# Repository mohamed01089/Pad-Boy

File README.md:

# Pad Boy
A simple macropad consists of 5 switches, a rotary encoder, custom pcp, and a case

## Dimensions 

PCP dimensions: 60.5 mm * 62.5 mm.
Case dimensions: 80.9 mm * 82.9 mm.

## BOM

- 5x Cherry MX Kew Switches
- 1x Rotary Encoder Witch Switch
- Seeduino XIAO RP2040
- 3D Printing
- PCP Manifacture

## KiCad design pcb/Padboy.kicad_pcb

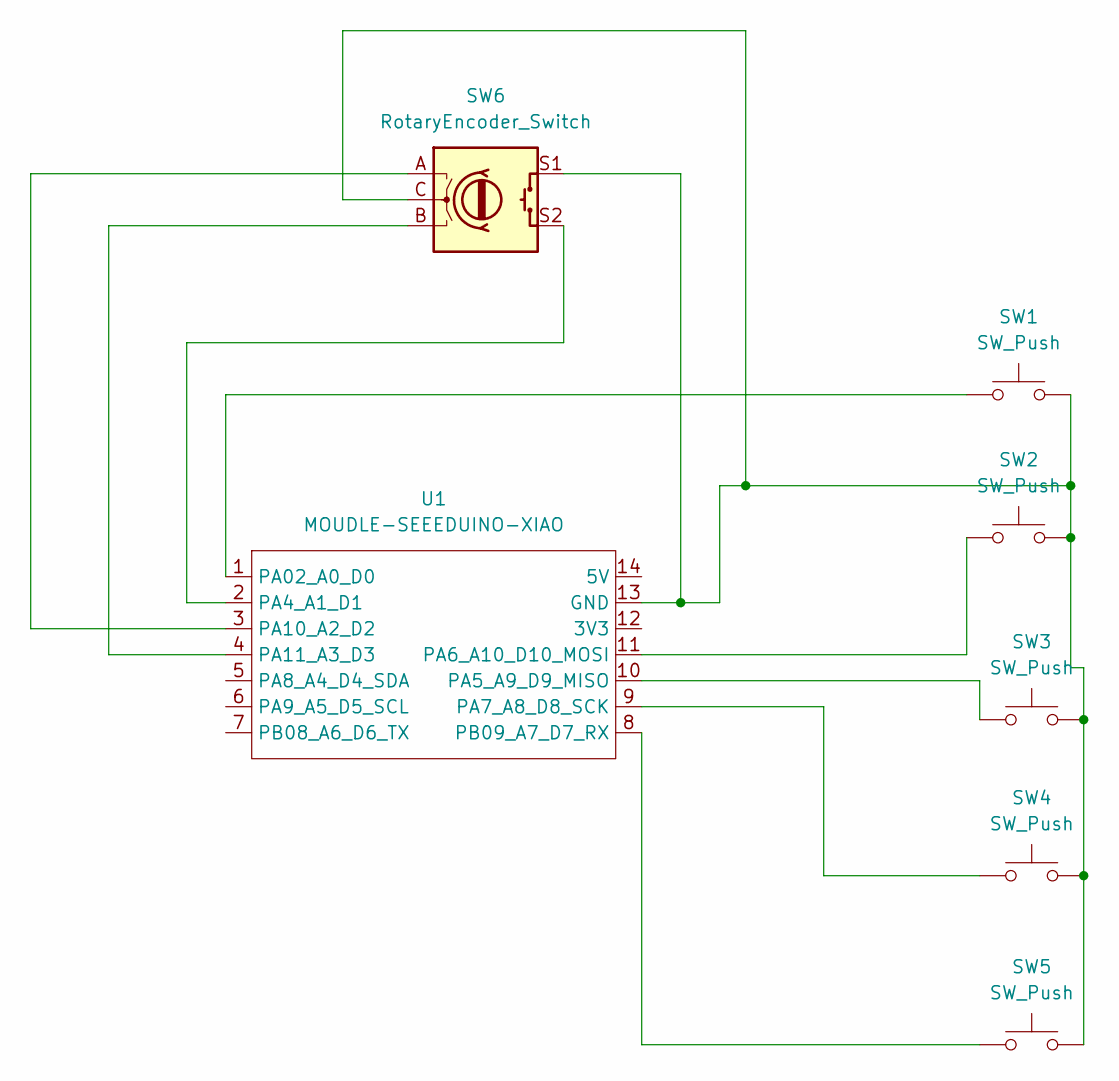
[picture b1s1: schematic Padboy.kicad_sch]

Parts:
SW1, SW2, SW3, SW4, SW5: SW_Push; SW_Cherry_MX_1.00u_PCB
SW6: RotaryEncoder_Switch; RotaryEncoder_Alps_EC11E-Switch_Vertical_H20mm
U1: MOUDLE-SEEEDUINO-XIAO; XIAO-Generic-Hybrid-14P-2.54-21X17.8MM

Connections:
unnamed: SW1.2, SW2.2, SW3.2, SW4.2, SW5.2, SW6.C, SW6.S1, U1.13 (GND)
unnamed: SW1.1, U1.1 (PA02_A0_D0)
unnamed: SW6.S2, U1.2 (PA4_A1_D1)
unnamed: SW3.1, U1.10 (PA5_A9_D9_MISO)
unnamed: SW2.1, U1.11 (PA6_A10_D10_MOSI)
unnamed: SW4.1, U1.9 (PA7_A8_D8_SCK)
unnamed: SW6.A, U1.3 (PA10_A2_D2)
unnamed: SW6.B, U1.4 (PA11_A3_D3)
unnamed: SW5.1, U1.8 (PB09_A7_D7_RX)

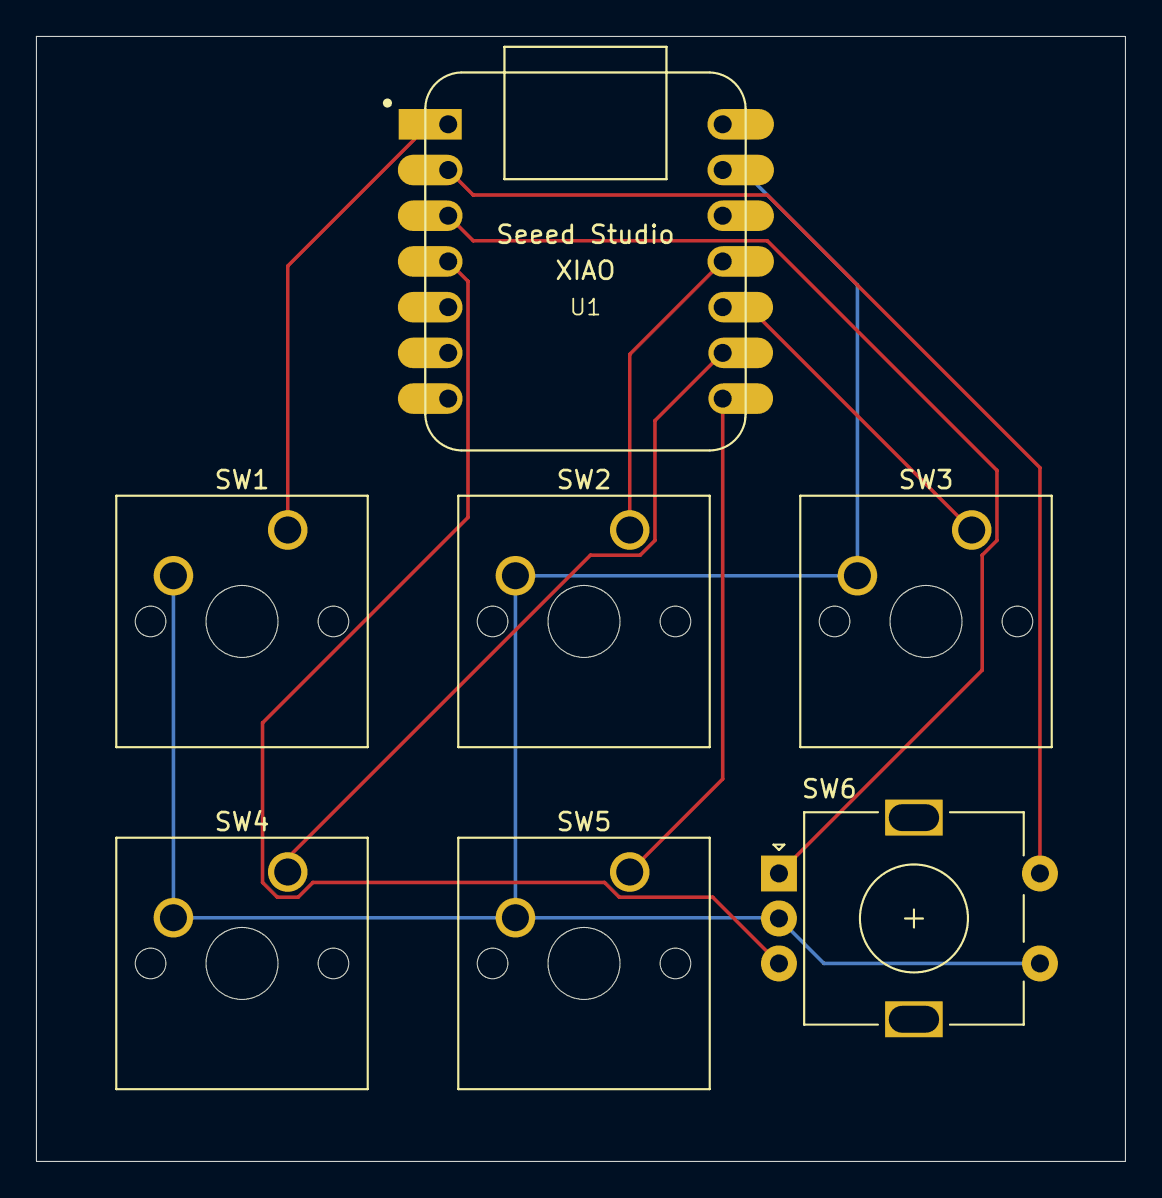
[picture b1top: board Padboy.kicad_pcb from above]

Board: 2 copper layers, 60.5 x 62.5 mm, 7 parts (0 on the bottom side), 9 nets.
